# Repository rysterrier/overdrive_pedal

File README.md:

# overdrive_pedal
Overdrive  pedal project

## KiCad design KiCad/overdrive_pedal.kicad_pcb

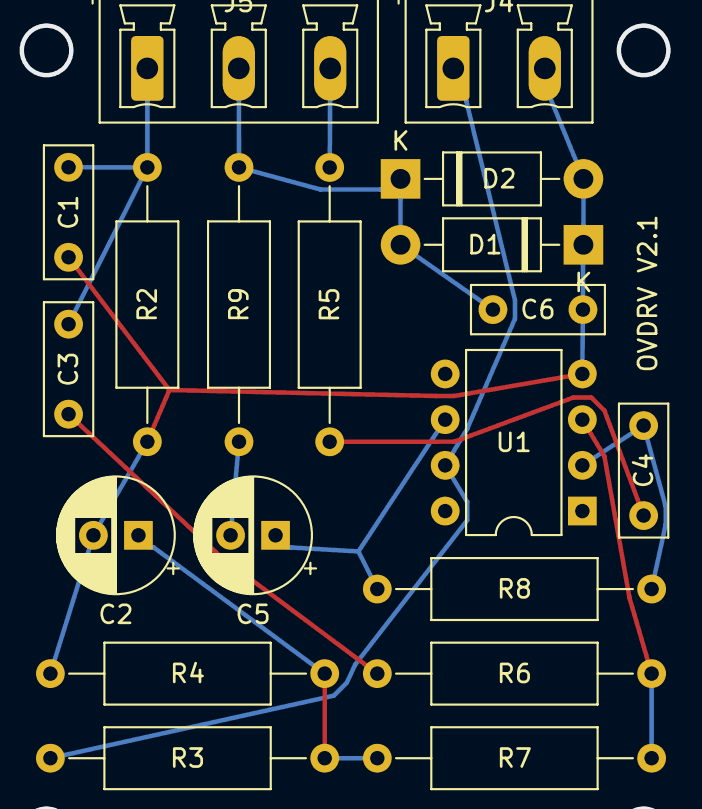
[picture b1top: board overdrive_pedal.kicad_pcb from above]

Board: 2 copper layers, 19 parts (0 on the bottom side), 12 nets.

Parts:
C1, C6: 0.0022uF; C_Rect_L7.2mm_W2.5mm_P5.00mm_FKS2_FKP2_MKS2_MKP2
C2: 10uF; CP_Radial_D6.3mm_P2.50mm
C3: 0.01uF; C_Rect_L7.2mm_W2.5mm_P5.00mm_FKS2_FKP2_MKS2_MKP2
C4: 0.047uF; C_Rect_L7.2mm_W2.5mm_P5.00mm_FKS2_FKP2_MKS2_MKP2
C5: 22uF; CP_Radial_D6.3mm_P2.50mm
D1: 1N914/ 1N4003; D_DO-41_SOD81_P10.16mm_Horizontal
D2: 1N914/1N4003; D_DO-41_SOD81_P10.16mm_Horizontal
J4: Connector_Power; PhoenixContact_MCV_1,5_2-G-5.08_1x02_P5.08mm_Vertical
J5: Out of Board Elements; PhoenixContact_MCV_1,5_3-G-5.08_1x03_P5.08mm_Vertical
R2: 1M5; R_Axial_DIN0309_L9.0mm_D3.2mm_P15.24mm_Horizontal
R3, R4: 20k; R_Axial_DIN0309_L9.0mm_D3.2mm_P15.24mm_Horizontal
R5: 47k; R_Axial_DIN0309_L9.0mm_D3.2mm_P15.24mm_Horizontal
R6, R9: 10k; R_Axial_DIN0309_L9.0mm_D3.2mm_P15.24mm_Horizontal
R7: 470k; R_Axial_DIN0309_L9.0mm_D3.2mm_P15.24mm_Horizontal
R8: 1M; R_Axial_DIN0309_L9.0mm_D3.2mm_P15.24mm_Horizontal
U1: LM741; DIP-8_W7.62mm

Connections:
+9V: J4.1, R3.2, U1.7
/100k_Poten_3: C6.1, D1.2, D2.1, J5.2, R9.1
/500k_Poten_3: J5.3, R5.2
/SW1A_2: C1.1, C3.2, J5.1, R2.1
GND: C1.2, C2.2, C6.2, D1.1, D2.2, J4.2, R2.2, R4.1, U1.4
unnamed: C2.1, R3.1, R4.2, R7.2
unnamed: C3.1, R6.1
unnamed: C4.1, R8.2, U1.2
unnamed: C4.2, R5.1
unnamed: C5.1, R8.1, U1.6
unnamed: C5.2, R9.2
unnamed: R6.2, R7.1, U1.3

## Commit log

2020-03-03 added new version
    Added pcb version with GND poligon
2020-03-03 added pcb
    Added main PCB, changed size from 50x50mm to 50x45mm and minor changes to layout
2020-05-05 added kicad files
    Redrew and rerouted PCB using TopoR router.
